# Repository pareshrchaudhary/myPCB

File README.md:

# myPCBs

1) AMS5047 is a 2^14 bit magnetic encoder and the board is custom made for modularity. Feel free to use the design and modify it according to your needs.

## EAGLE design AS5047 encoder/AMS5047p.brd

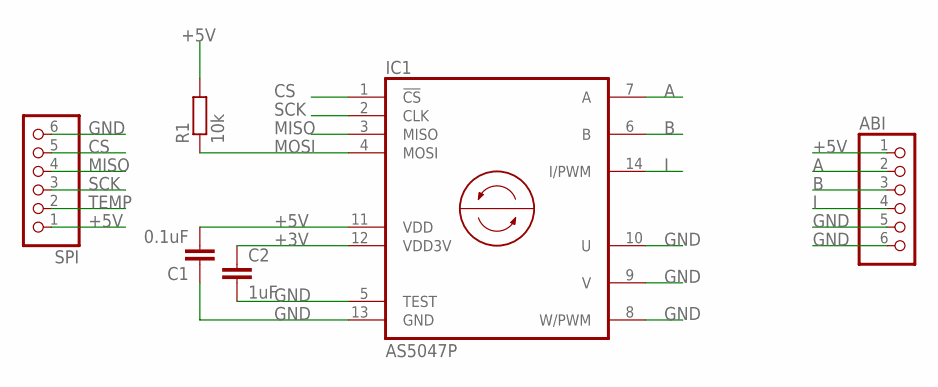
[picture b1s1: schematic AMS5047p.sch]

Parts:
ABI: PINHD-1X6; 1X06
C1: 0.1uF; C0603
C2: 1uF; C0603
IC1: AS5047P; TSSOP14
R1: 10k; R0603
SPI: PINHD-1X6; 1X06

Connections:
+3V: C2.1, IC1.12 (VDD3V)
+5V: ABI.1, C1.2, IC1.11 (VDD), R1.2, SPI.1
A: ABI.2, IC1.7 (A)
B: ABI.3, IC1.6 (B)
CS: IC1.1 (!CS!), SPI.5
GND: ABI.5, ABI.6, C1.1, C2.2, IC1.5 (TEST), IC1.8 (W/PWM), IC1.9 (V), IC1.10 (U), IC1.13 (GND), SPI.6
I: ABI.4, IC1.14 (I/PWM)
MISO: IC1.3 (MISO), SPI.4
MOSI: IC1.4 (MOSI), R1.1
SCK: IC1.2 (CLK), SPI.3
TEMP: SPI.2

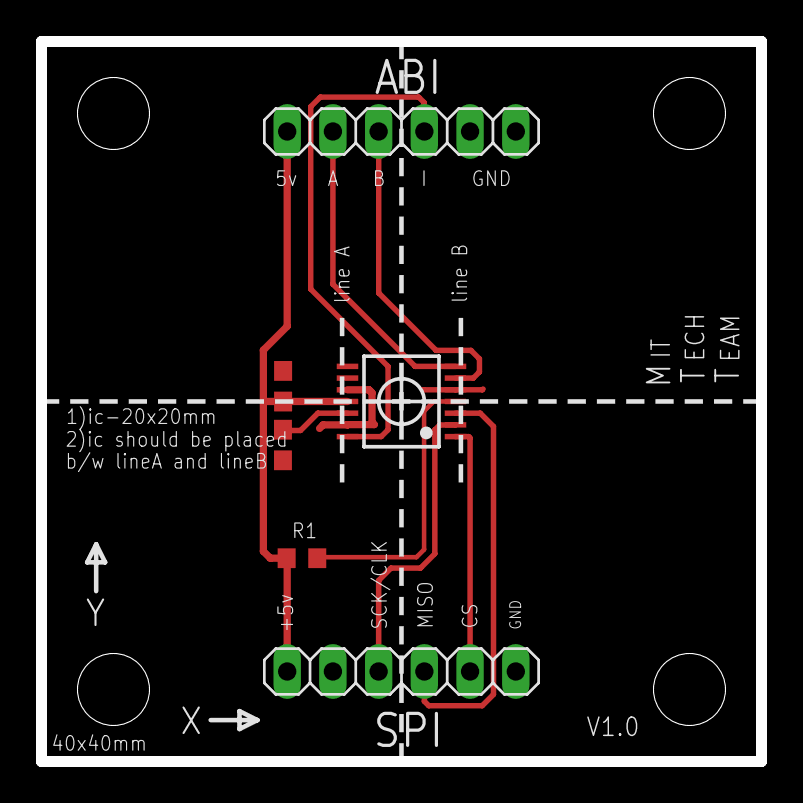
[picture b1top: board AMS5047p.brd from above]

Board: 2 copper layers, 40.0 x 40.0 mm, 6 parts (0 on the bottom side), 10 nets.

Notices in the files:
parts and their libraries:
ams: Copyright (C) 2015, Bob Starr
